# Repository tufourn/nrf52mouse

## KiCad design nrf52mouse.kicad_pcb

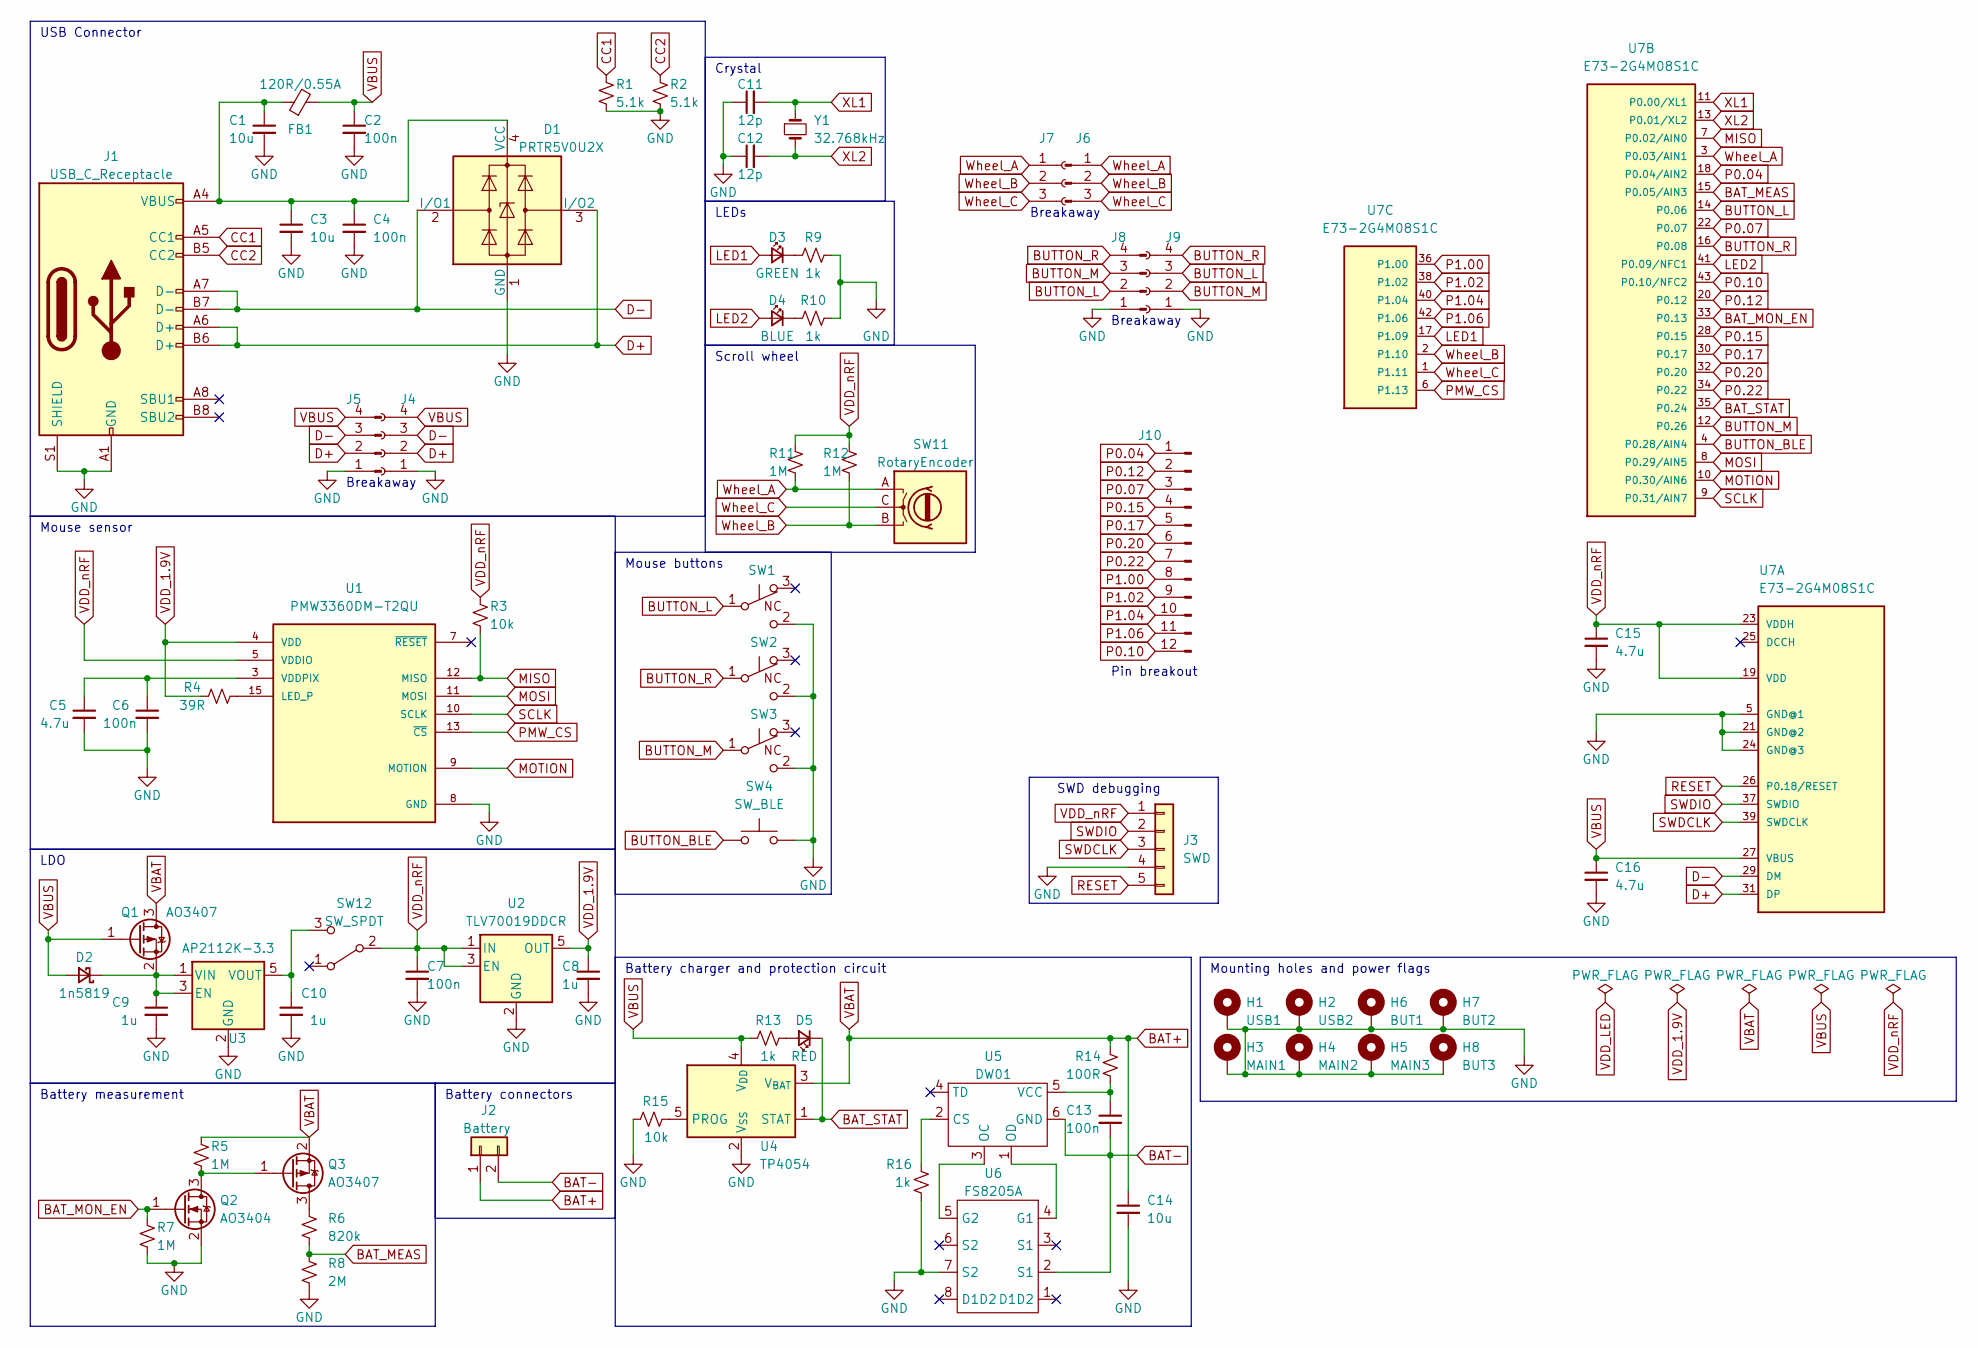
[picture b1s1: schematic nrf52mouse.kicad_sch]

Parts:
C1, C3, C14: 10u; C_0603_1608Metric_Pad1.08x0.95mm_HandSolder
C2, C4, C6, C7, C13: 100n; C_0603_1608Metric_Pad1.08x0.95mm_HandSolder
C5, C15, C16: 4.7u; C_0603_1608Metric_Pad1.08x0.95mm_HandSolder
C8, C9, C10: 1u; C_0603_1608Metric_Pad1.08x0.95mm_HandSolder
C11, C12: 12p; C_0603_1608Metric_Pad1.08x0.95mm_HandSolder
D1: PRTR5V0U2X; SOT-143
D2: 1n5819; D_SOD-323_HandSoldering
D3: GREEN; LED_0603_1608Metric_Pad1.05x0.95mm_HandSolder
D4: BLUE; LED_0603_1608Metric_Pad1.05x0.95mm_HandSolder
D5: RED; LED_0603_1608Metric_Pad1.05x0.95mm_HandSolder
FB1: 120R/0.55A; L_0805_2012Metric_Pad1.05x1.20mm_HandSolder
H1: USB1; MountingHole_2.5mm_Pad_Via
H2: USB2; MountingHole_2.5mm_Pad_Via
H3: MAIN1; MountingHole_2.5mm_Pad_Via
H4: MAIN2; MountingHole_2.5mm_Pad_Via
H5: MAIN3; MountingHole_2.5mm_Pad_Via
H6: BUT1; MountingHole_2.5mm_Pad_Via
H7: BUT2; MountingHole_2.5mm_Pad_Via
H8: BUT3; MountingHole_2.5mm_Pad_Via
J1: USB_C_Receptacle; USB-C_C168688
J2: Battery; JST_GH_BM02B-GHS-TBT_1x02-1MP_P1.25mm_Vertical
J3: SWD; PinHeader_1x05_P2.54mm_Vertical
J4: Conn_01x04_Socket; PinHeader_1x04_P2.54mm_Vertical
J5: Conn_01x04_Pin; PinHeader_1x04_P2.54mm_Vertical
J6: Conn_01x03_Pin; PinHeader_1x03_P2.54mm_Vertical
J7: Conn_01x03_Socket; PinHeader_1x03_P2.54mm_Vertical
J8: Conn_01x04_Pin; PinHeader_2x02_P2.54mm_Vertical
J9: Conn_01x04_Socket; PinHeader_2x02_P2.54mm_Vertical
J10: Conn_01x12_Pin; PinHeader_2x06_P2.54mm_Vertical
Q1: AO3407; SOT-23_Handsoldering
Q2: AO3404; SOT-23
Q3: AO3407; SOT-23
R1, R2: 5.1k; R_0603_1608Metric_Pad0.98x0.95mm_HandSolder
R3, R15: 10k; R_0603_1608Metric_Pad0.98x0.95mm_HandSolder
R4: 39R; R_0603_1608Metric_Pad0.98x0.95mm_HandSolder
R5, R7, R11, R12: 1M; R_0603_1608Metric_Pad0.98x0.95mm_HandSolder
R6: 820k; R_0603_1608Metric_Pad0.98x0.95mm_HandSolder
R8: 2M; R_0603_1608Metric_Pad0.98x0.95mm_HandSolder
R9, R10, R13, R16: 1k; R_0603_1608Metric_Pad0.98x0.95mm_HandSolder
R14: 100R; R_0603_1608Metric_Pad0.98x0.95mm_HandSolder
SW1, SW2, SW3: Mouse_Switch
SW4: SW_BLE; SW_SPST_TL3342
SW11: RotaryEncoder; Mouse_Encoder
SW12: SW_SPDT; SW_SPDT_PCM12
U1: PMW3360DM-T2QU; PMW3360; MANUFACTURER_PART_NUMBER PMW3360DM-T2QU
U2: TLV70019DDCR; SOT-23-5
U3: AP2112K-3.3; SOT-23-5
U4: TP4054; SOT-23-5
U5: DW01; SOT-23-6_Handsoldering
U6: FS8205A; TSSOP-8_4.4x3mm_P0.65mm
U7: E73-2G4M08S1C
Y1: 32.768kHz; Crystal_SMD_MicroCrystal_CM9V-T1A-2Pin_1.6x1.0mm_HandSolder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

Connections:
BAT+: C14.1, J2.1, Q1.3 (D), Q3.2 (S), R5.1, R14.1, U4.3 (V_{BAT})
BAT-: C13.2, J2.2, U5.6 (GND), U6.2 (S1)
BAT_MEAS: R6.2, R8.1, U7.15 (P0.05/AIN3)
BAT_MON_EN: Q2.1 (G), R7.1, U7.33 (P0.13)
BAT_STAT: D5.1 (K), U4.1 (STAT), U7.35 (P0.24)
BUTTON_BLE: SW4.2, U7.4 (P0.28/AIN4); also elsewhere on the board
BUTTON_L: J8.2, J9.3, SW1.1 (B), U7.14 (P0.06)
BUTTON_M: J8.3, J9.2, SW3.1 (B), U7.12 (P0.26)
BUTTON_R: J8.4, J9.4, SW2.1 (B), U7.16 (P0.08)
CC1: J1.A5 (CC1), R1.1
CC2: J1.B5 (CC2), R2.1
D+: D1.3 (I/O2), J1.A6 (D+), J1.B6 (D+), J4.2, J5.2, U7.31 (DP)
D-: D1.2 (I/O1), J1.A7 (D-), J1.B7 (D-), J4.3, J5.3, U7.29 (DM)
GND: C1.2, C2.2, C3.2, C4.2, C5.2, C6.2, C7.2, C8.2, C9.2, C10.2, C11.1, C12.1, C14.2, C15.2, C16.2, D1.1 (GND), H1.1, H2.1, H3.1, H4.1, H5.1, H6.1, H7.1, H8.1, J1.A1 (GND), J1.A12 (GND), J1.B1 (GND), J1.B12 (GND), J1.S1 (SHIELD), J3.4, J4.1, J5.1, J8.1, J9.1, Q2.2 (S), R1.2, R2.2, R7.2, R8.2, R9.1, R10.1, R15.1, R16.2, SW1.2 (C), SW2.2 (C), SW3.2 (C), SW4.1, U1.8 (GND), U2.2 (GND), U3.2 (GND), U4.2 (V_{SS}), U6.7 (S2), U7.5 (GND@1), U7.21 (GND@2), U7.24 (GND@3); also elsewhere on the board
LED1: D3.2 (A), U7.17 (P1.09)
LED2: D4.2 (A), U7.41 (P0.09/NFC1)
MISO: R3.2, U1.12 (MISO), U7.7 (P0.02/AIN0)
MOSI: U1.11 (MOSI), U7.8 (P0.29/AIN5)
MOTION: U1.9 (MOTION), U7.10 (P0.30/AIN6)
unnamed: C1.1, C3.1, C4.1, D1.4 (VCC), FB1.1, J1.A4 (VBUS), J1.A9 (VBUS), J1.B4 (VBUS), J1.B9 (VBUS)
unnamed: C9.1, D2.1 (K), Q1.2 (S), U3.1 (VIN), U3.3 (EN)
unnamed: D3.1 (K), R9.2
unnamed: D4.1 (K), R10.2
unnamed: D5.2 (A), R13.1
unnamed: Q2.3 (D), Q3.1 (G), R5.2
unnamed: Q3.3 (D), R6.1
unnamed: C10.1, SW12.3 (C), U3.5 (VOUT)
unnamed: R4.2, U1.15 (LED_P)
unnamed: C5.1, C6.1, U1.3 (VDDPIX)
unnamed: R15.2, U4.5 (PROG)
unnamed: R16.1, U5.2 (CS)
unnamed: U5.3 (OC), U6.5 (G2)
unnamed: U5.1 (OD), U6.4 (G1)
unnamed: C13.1, R14.2, U5.5 (VCC)
P0.04: J10.1, U7.18 (P0.04/AIN2)
P0.07: J10.3, U7.22 (P0.07)
P0.10: J10.12, U7.43 (P0.10/NFC2)
P0.12: J10.2, U7.20 (P0.12)
P0.15: J10.4, U7.28 (P0.15)
P0.17: J10.5, U7.30 (P0.17)
P0.20: J10.6, U7.32 (P0.20)
P0.22: J10.7, U7.34 (P0.22)
P1.00: J10.8, U7.36 (P1.00)
P1.02: J10.9, U7.38 (P1.02)
P1.04: J10.10, U7.40 (P1.04)
P1.06: J10.11, U7.42 (P1.06)
PMW_CS: U1.13 (~CS), U7.6 (P1.13)
RESET: J3.5, U7.26 (P0.18/RESET)
SCLK: U1.10 (SCLK), U7.9 (P0.31/AIN7)
SWDCLK: J3.3, U7.39 (SWDCLK)
SWDIO: J3.2, U7.37 (SWDIO)
VBUS: C2.1, C16.1, D2.2 (A), FB1.2, J4.4, J5.4, Q1.1 (G), R13.2, U4.4 (V_{DD}), U7.27 (VBUS)
VDD_1.9V: C8.1, R4.1, U1.4 (VDD), U2.5 (OUT)
VDD_nRF: C7.1, C15.1, J3.1, R3.1, R11.1, R12.1, SW12.2 (B), U1.5 (VDDIO), U2.1 (IN), U2.3 (EN), U7.19 (VDD), U7.23 (VDDH)
Wheel_A: J6.1, J7.1, R11.2, SW11.A, U7.3 (P0.03/AIN1)
Wheel_B: J6.2, J7.2, R12.2, SW11.B, U7.2 (P1.10)
Wheel_C: J6.3, J7.3, SW11.C, U7.1 (P1.11)
XL1: C11.2, U7.11 (P0.00/XL1), Y1.1
XL2: C12.2, U7.13 (P0.01/XL2), Y1.2

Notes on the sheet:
LDO
Crystal
USB Connector
LEDs
Battery connectors
Mouse sensor
Breakaway
Mounting holes and power flags
Pin breakout
SWD debugging
Battery charger and protection circuit
Scroll wheel
Battery measurement
Mouse buttons

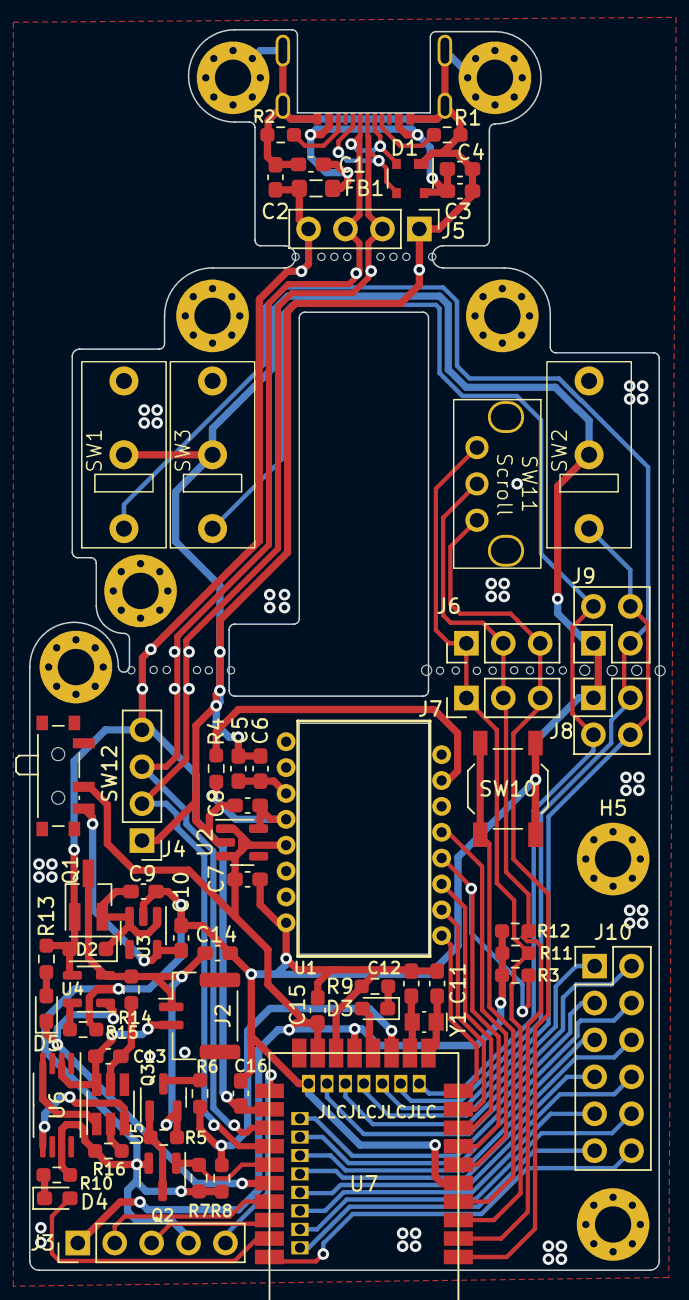
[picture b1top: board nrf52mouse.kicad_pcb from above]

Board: 2 copper layers, 43.3 x 85.3 mm, 73 parts (0 on the bottom side), 59 nets.

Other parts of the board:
SW10: SW_BLE; SW_SPST_TL3342

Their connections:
BUTTON_BLE: SW10.2; also elsewhere on the board
GND: SW10.1; also elsewhere on the board

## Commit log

2023-06-22 initial
